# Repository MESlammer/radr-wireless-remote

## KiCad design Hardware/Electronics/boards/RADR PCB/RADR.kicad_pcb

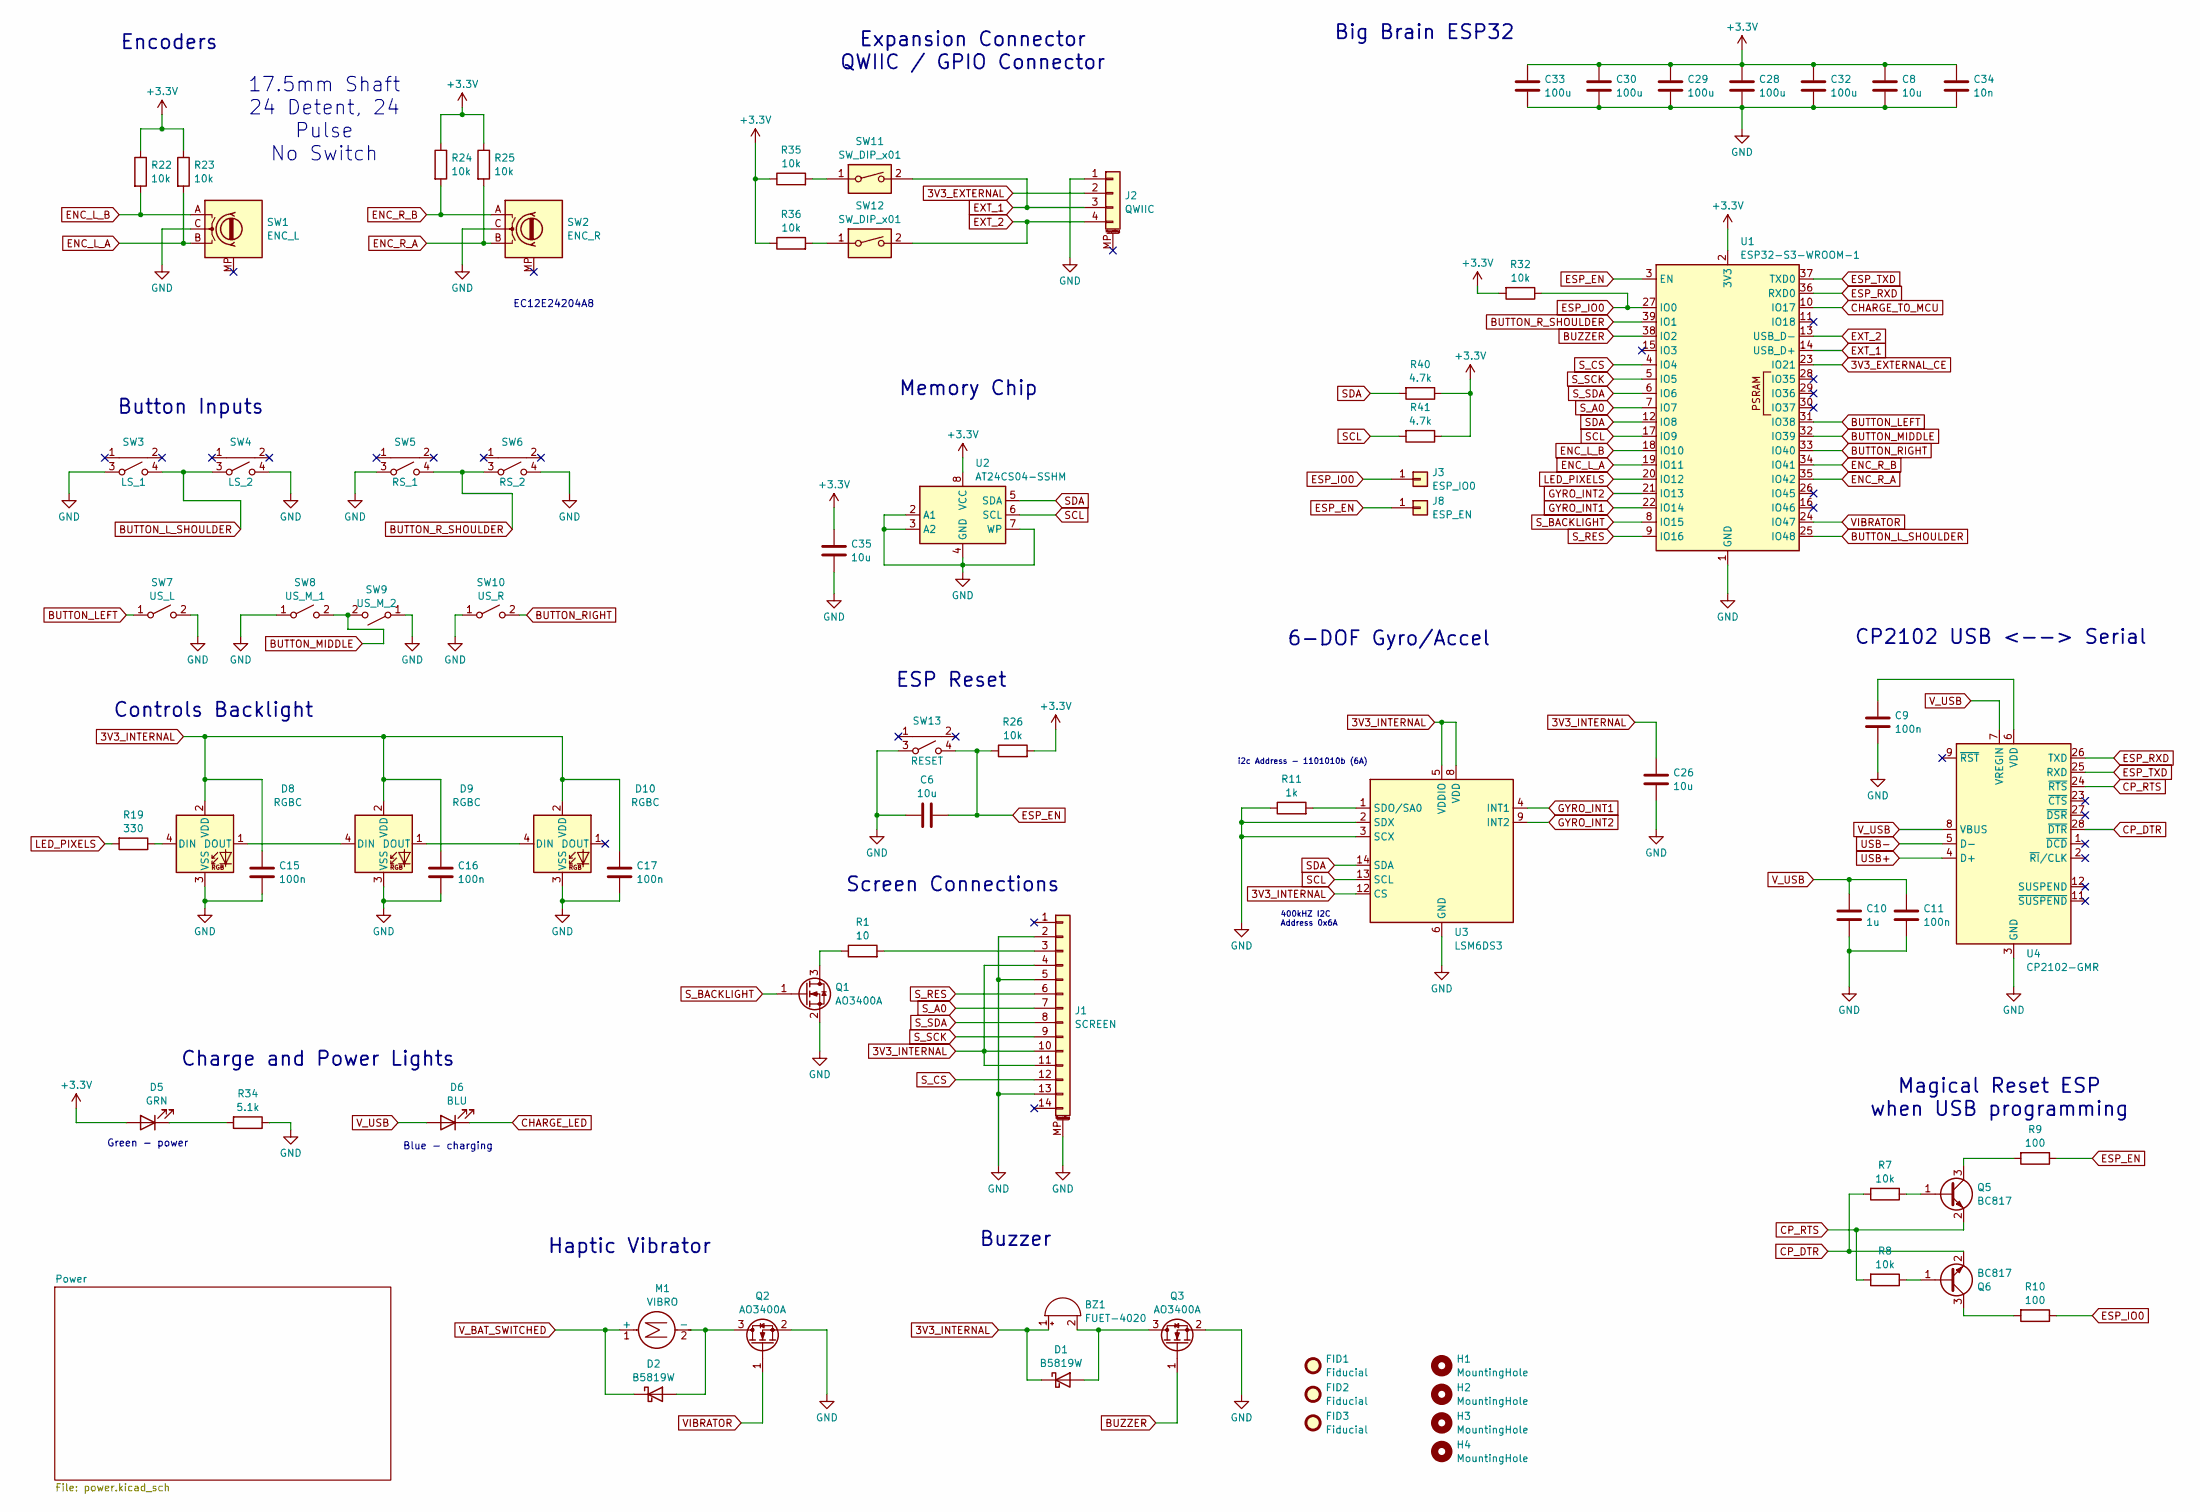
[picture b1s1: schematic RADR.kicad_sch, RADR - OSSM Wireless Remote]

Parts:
BZ1: FUET-4020; Buzzer_FUET-4020_SMD_L4.0-W4.0-P3.50-L; MPN FUET-4020; lcsc-bom-key C391027
C6, C8, C26, C35: 10u; C_0402_1005Metric; MPN CL05A105KA5NQNC; lcsc-bom-key C52923
C9, C11, C15, C16, C17: 100n; C_0402_1005Metric; MPN CL05A104KA5NNNC; lcsc-bom-key C100072
C10: 1u; C_0402_1005Metric; MPN CL05A105KA5NQNC; lcsc-bom-key C52923
C28, C29, C30, C32, C33: 100u; C_1206_3216Metric; MPN CL31A107MQHNNNE; lcsc-bom-key C15008
C34: 10n; C_0402_1005Metric; MPN CL05B103KB5NNNC; lcsc-bom-key C15195
D1, D2: B5819W; D_SOD-123; MPN B5819W; lcsc-bom-key C5345968
D5: GRN; LED_0603_1608Metric; MPN TJ-S1706SW6TGLC2G-A5; lcsc-bom-key C273616
D6: BLU; LED_0603_1608Metric; MPN TJ-S1706SW6TGLC6B-A5; lcsc-bom-key C273617
D8, D9, D10: RGBC; LED_Xinglight_XL-1010RGBC-WS2812B_1.0mm_1.0mm; MPN XL-1010RGBC-2812B; lcsc-bom-key C5349953
FID1, FID2, FID3: Fiducial; Fiducial_1mm_Mask3mm
H1, H2, H3, H4: MountingHole; MountingHole_3.5mm
J1: SCREEN; AFC01-S14FCA-00; MPN AFC01-S14FCA-00; lcsc-bom-key C262663
J2: QWIIC; JST_SH_SM04B-SRSS-TB_1x04-1MP_P1.00mm_Horizontal; MPN SM04B-SRSS-TB(LF)(SN); lcsc-bom-key C160404
J3: ESP_IO0; TestPoint_THTPad_D1.0mm_Drill0.5mm
J8: ESP_EN; TestPoint_THTPad_D1.0mm_Drill0.5mm
M1: VIBRO; Vybronics_VZ30C1T8219732L; MPN Z3OC1T8219731; lcsc-bom-key C2894731
Q1, Q2, Q3: AO3400A; SOT-23; MPN AO3400A; lcsc-bom-key C20917
Q5, Q6: BC817; SOT-23; MPN BC817-25,215; lcsc-bom-key C39828
R1: 10; R_0603_1608Metric; MPN RC0603JR-0710RL; lcsc-bom-key C109317
R7, R8, R22, R23, R24, R25, R26, R32, R35, R36: 10k; R_0402_1005Metric; MPN RC0402FR-0710KL; lcsc-bom-key C60490
R9, R10: 100; R_0402_1005Metric; MPN RC0402FR-07100RL; lcsc-bom-key C106232
R11: 1k; R_0402_1005Metric; MPN RC0402FR-071KL; lcsc-bom-key C106235
R19: 330; R_0402_1005Metric; MPN RC0402FR-07330RL; lcsc-bom-key C105875
R34: 5.1k; R_0402_1005Metric; MPN RC0402FR-075K1L; lcsc-bom-key C105872
R40, R41: 4.7k; R_0402_1005Metric; MPN RC0402FR-074K7L; lcsc-bom-key C105871
SW1: ENC_L; RotaryEncoder_Alps_EC12E_Vertical_H20mm; MPN EC12E24204A8; lcsc-bom-key C470598
SW2: ENC_R; RotaryEncoder_Alps_EC12E_Vertical_H20mm; MPN EC12E24204A8; lcsc-bom-key C470598
SW3: LS_1; SW-SMD_TS24CA; MPN TS24CA; lcsc-bom-key C393942
SW4: LS_2; SW-SMD_TS24CA; MPN TS24CA; lcsc-bom-key C393942
SW5: RS_1; SW-SMD_TS24CA; MPN TS24CA; lcsc-bom-key C393942
SW6: RS_2; SW-SMD_TS24CA; MPN TS24CA; lcsc-bom-key C393942
SW7: US_L; SW_PUSH_6mm; MPN TC-6610-9-260G; lcsc-bom-key C2845257
SW8: US_M_1; SW_PUSH_6mm; MPN TC-6610-9-260G; lcsc-bom-key C2845257
SW9: US_M_2; SW_PUSH_6mm; MPN TC-6610-9-260G; lcsc-bom-key C2845257
SW10: US_R; SW_PUSH_6mm; MPN TC-6610-9-260G; lcsc-bom-key C2845257
SW11, SW12: SW_DIP_x01; SW_DIP_SPSTx01_Slide_2.54-1P_TPGT; MPN 2.54-1P TPGT; lcsc-bom-key C7421519
SW13: RESET; SW-SMD_TS24CA; MPN TS24CA; lcsc-bom-key C393942
U1: ESP32-S3-WROOM-1; MPN C2913202 ESP32-S3-WROOM-1-N16R8 ESPRESS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; lcsc-bom-key C2913202
U2: AT24CS04-SSHM; SOIC-8_3.9x4.9mm_P1.27mm; MPN AT24C04C-SSHM-T; lcsc-bom-key C6205
U3: LSM6DS3; LGA-14_3x2.5mm_P0.5mm_LayoutBorder3x4y; MPN LSM6DS3TR; lcsc-bom-key C95230
U4: CP2102-GMR; QFN-28-1EP_5x5mm_P0.5mm_EP3.35x3.35mm; MPN CP2102-GMR; lcsc-bom-key C6568

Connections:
3V3_EXTERNAL: J2.2; also elsewhere on the board
3V3_EXTERNAL_CE: U1.23 (IO21); also elsewhere on the board
3V3_INTERNAL: BZ1.1 (+), C15.2, C16.2, C17.2, C26.1, D1.1 (K), D8.2 (VDD), D9.2 (VDD), D10.2 (VDD), J1.4, J1.10, J1.11, U3.5 (VDDIO), U3.8 (VDD), U3.12 (CS); also elsewhere on the board
+3.3V: C8.1, C28.1, C29.1, C30.1, C32.1, C33.1, C34.1, C35.1, D5.2 (A), R22.1, R23.1, R24.1, R25.1, R26.2, R32.2, R35.1, R36.1, R40.1, R41.1, U1.2 (3V3), U2.8 (VCC); also elsewhere on the board
BUTTON_LEFT: SW7.1 (A), U1.31 (IO38)
BUTTON_L_SHOULDER: SW3.4 (B), SW4.3 (A), U1.25 (IO48)
BUTTON_MIDDLE: SW8.2 (B), SW9.2 (B), U1.32 (IO39)
BUTTON_RIGHT: SW10.2 (B), U1.33 (IO40)
BUTTON_R_SHOULDER: SW5.4 (B), SW6.3 (A), U1.39 (IO1)
BUZZER: Q3.1 (G), U1.38 (IO2)
CHARGE_LED: D6.1 (K); also elsewhere on the board
CHARGE_TO_MCU: U1.10 (IO17); also elsewhere on the board
CP_DTR: Q6.2 (E), R7.2, U4.28 (~DTR)
CP_RTS: Q5.2 (E), R8.2, U4.24 (~RTS)
ENC_L_A: R23.2, SW1.B, U1.19 (IO11)
ENC_L_B: R22.2, SW1.A, U1.18 (IO10)
ENC_R_A: R25.2, SW2.B, U1.35 (IO42)
ENC_R_B: R24.2, SW2.A, U1.34 (IO41)
ESP_EN: C6.1, J8.1 (Pin_1_1), R9.1, R26.1, SW13.4 (B), U1.3 (EN)
ESP_IO0: J3.1 (Pin_1_1), R10.1, R32.1, U1.27 (IO0)
ESP_RXD: U1.36 (RXD0), U4.26 (TXD)
ESP_TXD: U1.37 (TXD0), U4.25 (RXD)
EXT_1: J2.3, SW11.2, U1.14 (USB_D+)
EXT_2: J2.4, SW12.2, U1.13 (USB_D-)
GND: C6.2, C8.2, C9.2, C10.2, C11.2, C15.1, C16.1, C17.1, C26.2, C28.2, C29.2, C30.2, C32.2, C33.2, C34.2, C35.2, D8.3 (VSS), D9.3 (VSS), D10.3 (VSS), J1.2, J1.5, J1.13, J1.MP (MountPin), J2.1, Q1.2 (S), Q2.2 (S), Q3.2 (S), R11.1, R34.1, SW1.C, SW2.C, SW3.3 (A), SW4.4 (B), SW5.3 (A), SW6.4 (B), SW7.2 (B), SW8.1 (A), SW9.1 (A), SW10.1 (A), SW13.3 (A), U1.1 (GND), U1.40 (GND), U1.41 (GND), U2.2 (A1), U2.3 (A2), U2.4 (GND), U2.7 (WP), U3.2 (SDX), U3.3 (SCX), U3.6 (GND), U3.7 (GND), U4.3 (GND), U4.29 (GND); also elsewhere on the board
GYRO_INT1: U1.22 (IO14), U3.4 (INT1)
GYRO_INT2: U1.21 (IO13), U3.9 (INT2)
LED_PIXELS: R19.2, U1.20 (IO12)
unnamed: BZ1.2 (-), D1.2 (A), Q3.3 (D)
unnamed: D2.2 (A), M1.2 (-), Q2.3 (D)
unnamed: D5.1 (K), R34.2
unnamed: D8.4 (DIN), R19.1
unnamed: D8.1 (DOUT), D9.4 (DIN)
unnamed: D9.1 (DOUT), D10.4 (DIN)
unnamed: J1.3, R1.2
unnamed: Q1.3 (D), R1.1
unnamed: Q5.1 (B), R7.1
unnamed: Q5.3 (C), R9.2
unnamed: Q6.1 (B), R8.1
unnamed: Q6.3 (C), R10.2
unnamed: R35.2, SW11.1
unnamed: R36.2, SW12.1
unnamed: R11.2, U3.1 (SDO/SA0)
unnamed: C9.1, U4.6 (VDD)
SCL: R41.2, U1.17 (IO9), U2.6 (SCL), U3.13 (SCL); also elsewhere on the board
SDA: R40.2, U1.12 (IO8), U2.5 (SDA), U3.14 (SDA); also elsewhere on the board
S_A0: J1.7, U1.7 (IO7)
S_BACKLIGHT: Q1.1 (G), U1.8 (IO15)
S_CS: J1.12, U1.4 (IO4)
S_RES: J1.6, U1.9 (IO16)
S_SCK: J1.9, U1.5 (IO5)
S_SDA: J1.8, U1.6 (IO6)
USB+: U4.4 (D+); also elsewhere on the board
USB-: U4.5 (D-); also elsewhere on the board
VIBRATOR: Q2.1 (G), U1.24 (IO47)
V_BAT_SWITCHED: D2.1 (K), M1.1 (+); also elsewhere on the board
V_USB: C10.1, C11.1, D6.2 (A), U4.7 (VREGIN), U4.8 (VBUS); also elsewhere on the board

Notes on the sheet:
EC12E24204A8
Haptic Vibrator
6-DOF Gyro/Accel
Magical Reset ESP when USB programming
i2c Address - 1101010b (6A)
Button Inputs
Expansion Connector QWIIC / GPIO Connector
Controls Backlight
Big Brain ESP32
Green - power
Memory Chip
ESP Reset
Buzzer
CP2102 USB <--> Serial
400kHZ I2C Address 0x6A
Blue - charging
Screen Connections
Charge and Power Lights
Encoders
17.5mm Shaft 24 Detent, 24 Pulse No Switch

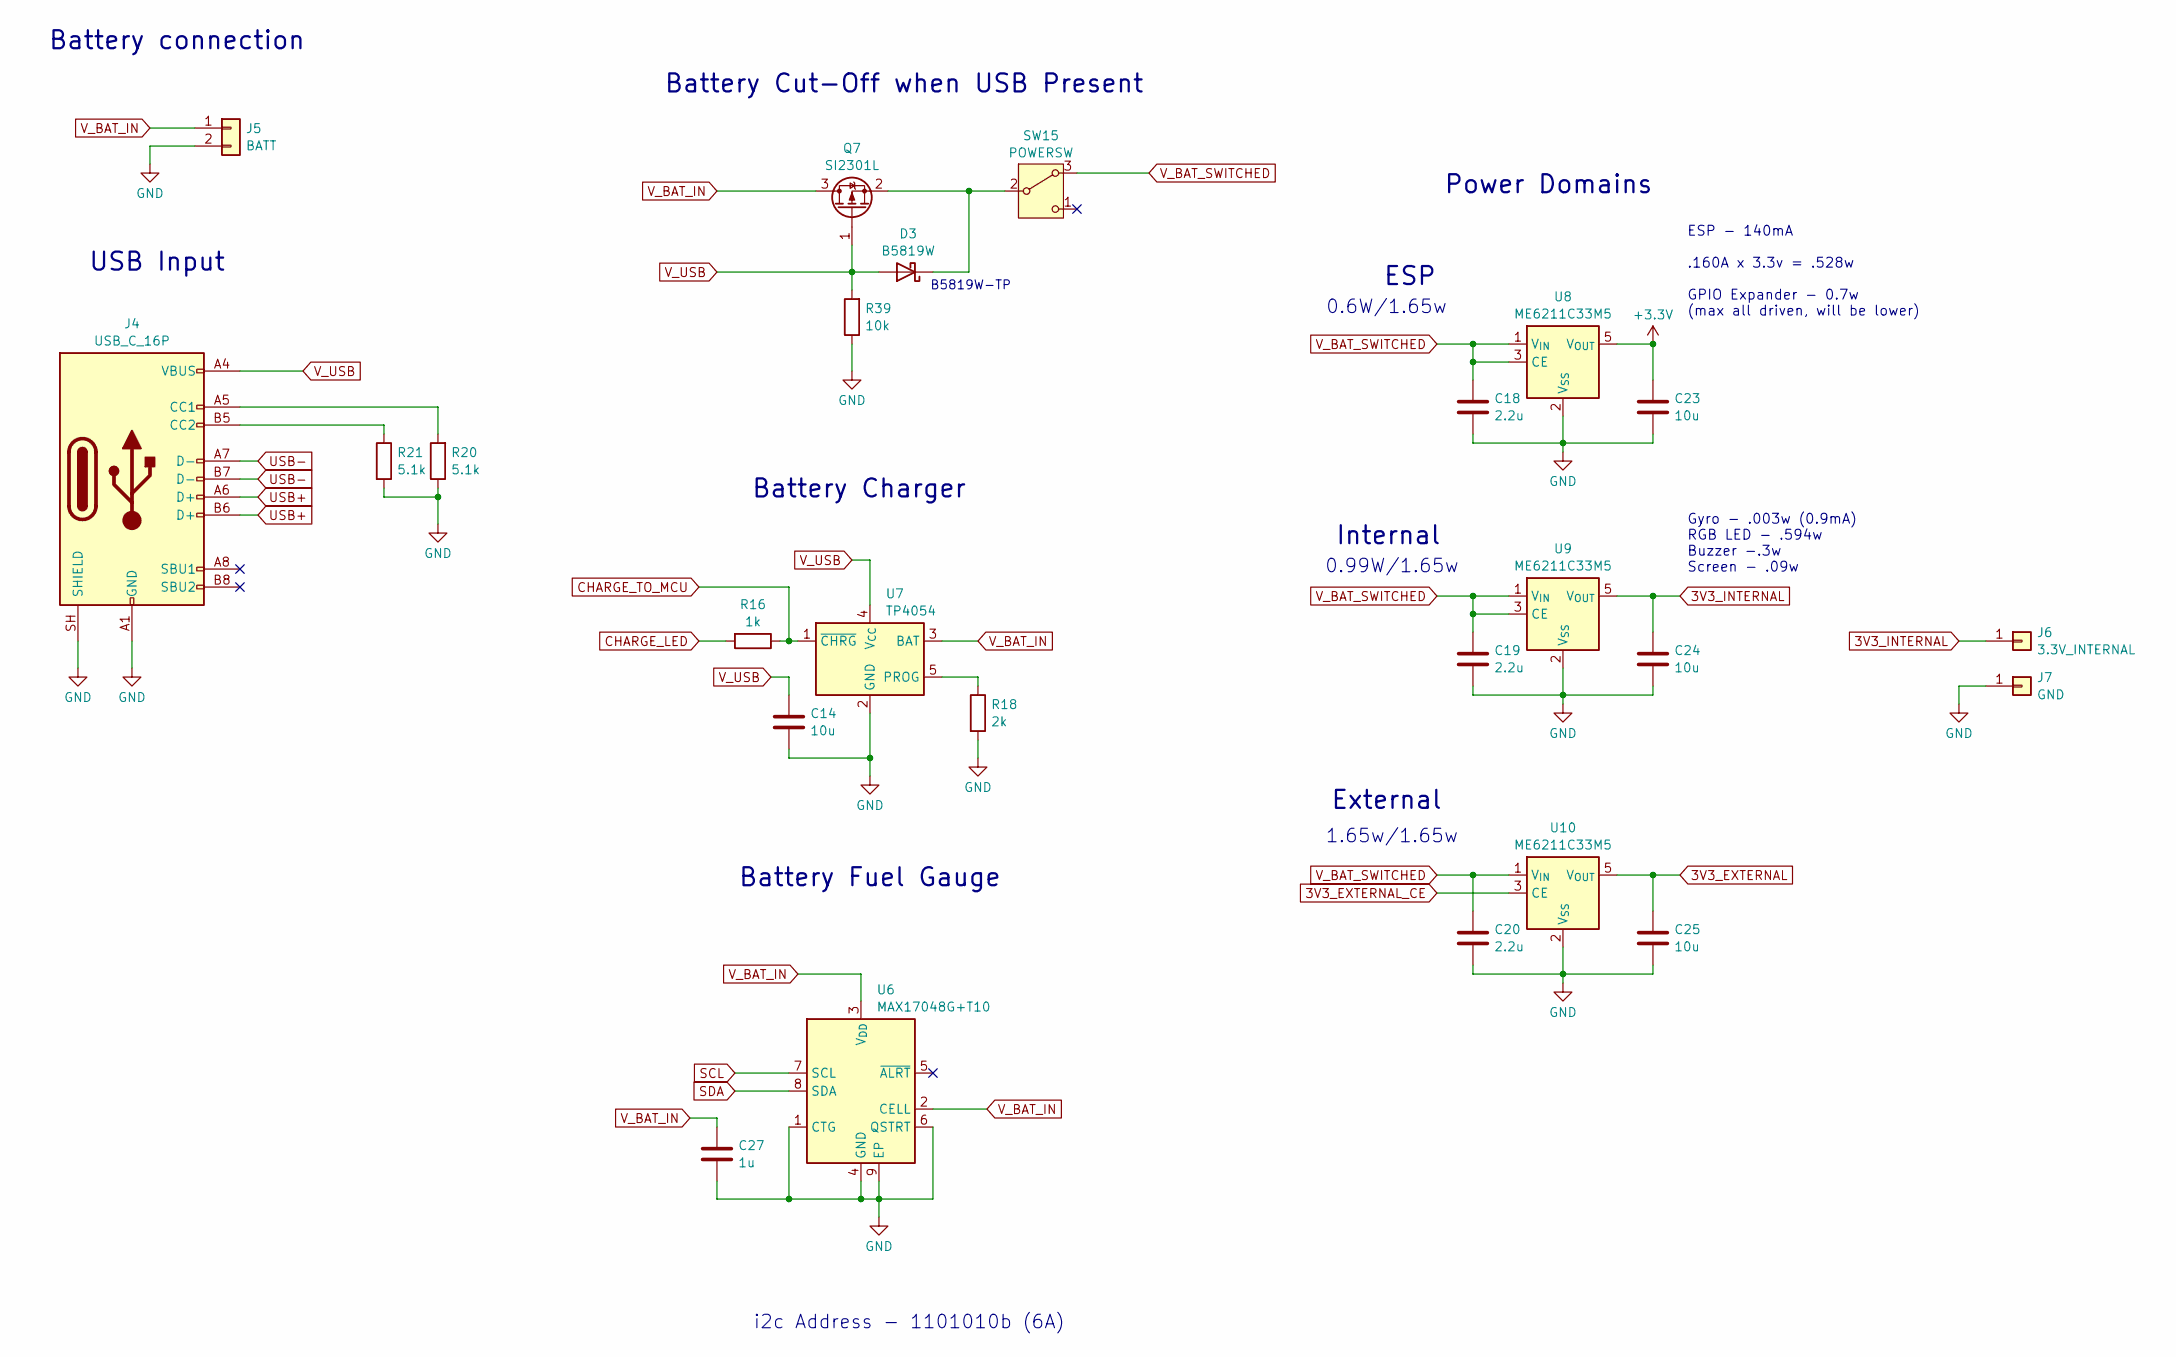
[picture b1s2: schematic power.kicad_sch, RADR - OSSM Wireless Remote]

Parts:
C14, C23, C24, C25: 10u; C_0402_1005Metric; MPN CL05A105KA5NQNC; lcsc-bom-key C52923
C18, C19, C20: 2.2u; C_0402_1005Metric; MPN CL05A225KO5NQNC; lcsc-bom-key C170151
C27: 1u; C_0402_1005Metric; MPN CL05A105KA5NQNC; lcsc-bom-key C52923
D3: B5819W; D_SOD-123; MPN B5819W; lcsc-bom-key C5345968
J4: USB_C_16P; USB_C_Receptacle_HRO_TYPE-C-31-M-12; MPN TYPE-C-31-M-12; lcsc-bom-key C165948
J5: BATT; JST_PH_S2B-PH-K_1x02_P2.00mm_Horizontal; MPN S2B-PH-K(LF)(SN); lcsc-bom-key C265016
J6: 3.3V_INTERNAL; TestPoint_THTPad_2.0x2.0mm_Drill1.0mm
J7: GND; TestPoint_THTPad_2.0x2.0mm_Drill1.0mm
Q7: SI2301L; SOT-23; MPN SI2301; lcsc-bom-key C727151
R16: 1k; R_0402_1005Metric; MPN RC0402FR-071KL; lcsc-bom-key C106235
R18: 2k; R_0402_1005Metric; MPN RC0402FR-072KL; lcsc-bom-key C60488
R20, R21: 5.1k; R_0402_1005Metric; MPN RC0402FR-075K1L; lcsc-bom-key C105872
R39: 10k; R_0402_1005Metric; MPN RC0402FR-0710KL; lcsc-bom-key C60490
SW15: POWERSW; SW_Slide_SPDT_Angled_CK_OS102011MA1Q; MPN SK12D07VG5; lcsc-bom-key C431548
U6: MAX17048G+T10; DFN-8-1EP_2x2mm_P0.5mm_EP0.9x1.5mm; MPN MAX17048G+T10; lcsc-bom-key C2682616
U7: TP4054; SOT-23-5; MPN TP4054; lcsc-bom-key C5381776
U8, U9, U10: ME6211C33M5; SOT-23-5; MPN ME6211C33R5G; lcsc-bom-key C235316

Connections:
3V3_EXTERNAL: C25.1, U10.5 (V_{OUT}); also elsewhere on the board
3V3_EXTERNAL_CE: U10.3 (CE); also elsewhere on the board
3V3_INTERNAL: C24.1, J6.1 (Pin_1_1), U9.5 (V_{OUT}); also elsewhere on the board
+3.3V: C23.1, U8.5 (V_{OUT}); also elsewhere on the board
CHARGE_LED: R16.2; also elsewhere on the board
CHARGE_TO_MCU: R16.1, U7.1 (~CHRG); also elsewhere on the board
GND: C14.2, C18.2, C19.2, C20.2, C23.2, C24.2, C25.2, C27.2, J4.A1 (GND), J4.A12 (GND), J4.B1 (GND), J4.B12 (GND), J4.SH (SHIELD), J5.2, J7.1 (Pin_1_1), R18.2, R20.1, R21.2, R39.1, U6.1 (CTG), U6.4 (GND), U6.6 (QSTRT), U6.9 (EP), U7.2 (GND), U8.2 (V_{SS}), U9.2 (V_{SS}), U10.2 (V_{SS}); also elsewhere on the board
unnamed: D3.1 (K), Q7.2 (S), SW15.2 (B)
unnamed: J4.A5 (CC1), R20.2
unnamed: J4.B5 (CC2), R21.1
unnamed: R18.1, U7.5 (PROG)
SCL: U6.7 (SCL); also elsewhere on the board
SDA: U6.8 (SDA); also elsewhere on the board
USB+: J4.A6 (D+), J4.B6 (D+); also elsewhere on the board
USB-: J4.A7 (D-), J4.B7 (D-); also elsewhere on the board
V_BAT_IN: C27.1, J5.1, Q7.3 (D), U6.2 (CELL), U6.3 (V_{DD}), U7.3 (BAT)
V_BAT_SWITCHED: C18.1, C19.1, C20.1, SW15.3 (A), U8.1 (V_{IN}), U8.3 (CE), U9.1 (V_{IN}), U9.3 (CE), U10.1 (V_{IN}); also elsewhere on the board
V_USB: C14.1, D3.2 (A), J4.A4 (VBUS), J4.A9 (VBUS), J4.B4 (VBUS), J4.B9 (VBUS), Q7.1 (G), R39.2, U7.4 (V_{CC}); also elsewhere on the board

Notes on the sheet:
1.65w/1.65w
Battery connection
Battery Charger
0.99W/1.65w
Power Domains
Battery Fuel Gauge
External
B5819W-TP
ESP
USB Input
Battery Cut-Off when USB Present
i2c Address - 1101010b (6A)
Internal
0.6W/1.65w
ESP - 140mA .160A x 3.3v = .528w GPIO Expander - 0.7w (max all driven, will be lower)
Gyro - .003w (0.9mA) RGB LED - .594w Buzzer -.3w Screen - .09w

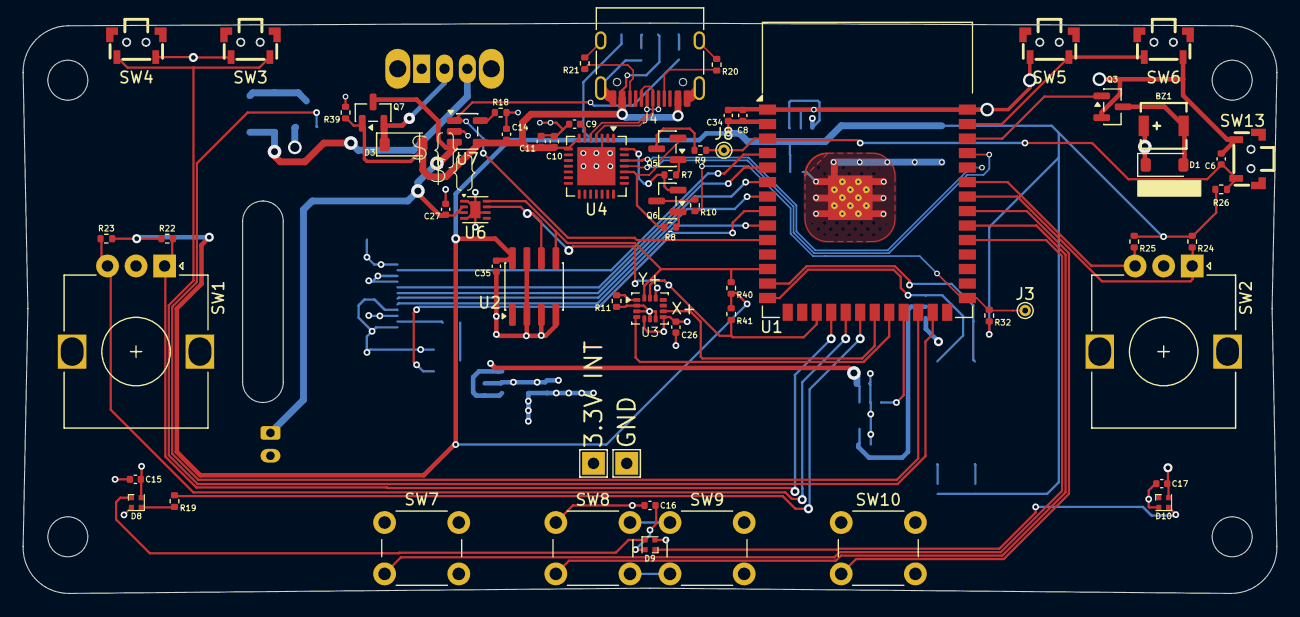
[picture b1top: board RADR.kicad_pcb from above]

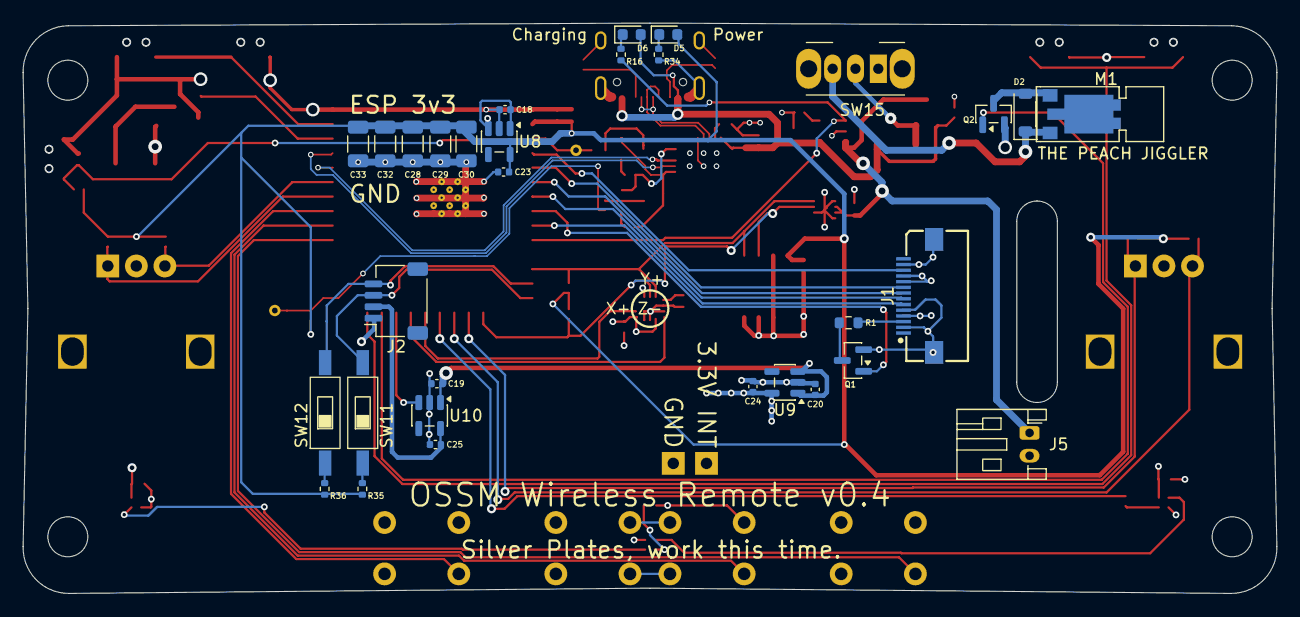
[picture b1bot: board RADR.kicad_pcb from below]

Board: 4 copper layers, 109.8 x 50.0 mm, 98 parts (31 on the bottom side), 62 nets.

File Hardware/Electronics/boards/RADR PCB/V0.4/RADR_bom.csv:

"Reference","Qty","Value","Footprint","Datasheet","lcsc-bom-key","MPN","MFG","Characteristics","DNP","Exclude from BOM","Exclude from Board"
"BZ1","1","FUET-4020","RADR:Buzzer_FUET-4020_SMD_L4.0-W4.0-P3.50-L","https://www.lcsc.com/datasheet/C391027.pdf","C391027","FUET-4020","FUET","","","",""
"C6,C8,C14,C23,C24,C25,C26,C35","8","10u","Capacitor_SMD:C_0402_1005Metric","https://www.lcsc.com/datasheet/C52923.pdf","C52923","CL05A105KA5NQNC","Samsung Electro-Mechanics","","","",""
"C9,C11,C15,C16,C17","5","100n","Capacitor_SMD:C_0402_1005Metric","https://www.lcsc.com/datasheet/C100072.pdf","C100072","CL05A104KA5NNNC","Samsung Electro-Mechanics","","","",""
"C10,C27","2","1u","Capacitor_SMD:C_0402_1005Metric","https://www.lcsc.com/datasheet/C52923.pdf","C52923","CL05A105KA5NQNC","Samsung Electro-Mechanics","","","",""
"C18,C19,C20","3","2.2u","Capacitor_SMD:C_0402_1005Metric","https://www.lcsc.com/datasheet/C170151.pdf","C170151","CL05A225KO5NQNC","Samsung Electro-Mechanics","","","",""
"C28,C29,C30,C32,C33","5","100u","Capacitor_SMD:C_1206_3216Metric","https://www.lcsc.com/datasheet/C15008.pdf","C15008","CL31A107MQHNNNE","Samsung Electro-Mechanics","","","",""
"C34","1","10n","Capacitor_SMD:C_0402_1005Metric","https://www.lcsc.com/datasheet/C15195.pdf","C15195","CL05B103KB5NNNC","CL05B103KB5NNNC","","","",""
"D1,D2,D3","3","B5819W","Diode_SMD:D_SOD-123","https://www.lcsc.com/datasheet/C5345968.pdf","C5345968","B5819W","HXY MOSFET","","","",""
"D5","1","GRN","LED_SMD:LED_0603_1608Metric","https://www.lcsc.com/datasheet/C273616.pdf","C273616","TJ-S1706SW6TGLC2G-A5","TOGIALED","Green","","",""
"D6","1","BLU","LED_SMD:LED_0603_1608Metric","https://www.lcsc.com/datasheet/C273617.pdf","C273617","TJ-S1706SW6TGLC6B-A5","TOGIALED","Blue","","",""
"D8,D9,D10","3","RGBC","LED_SMD:LED_XL-1010RGBC-WS2812B_1.0x1.0mm","https://www.lcsc.com/datasheet/C5349953.pdf","C5349953","XL-1010RGBC-2812B","XINGLIGHT","","","",""
"J1","1","SCREEN","RADR:AFC01-S14FCA-00","https://www.lcsc.com/datasheet/C262663.pdf","C262663","AFC01-S14FCA-00","JUSHUO","","","",""
"J2","1","QWIIC","Connector_JST:JST_SH_SM04B-SRSS-TB_1x04-1MP_P1.00mm_Horizontal","https://www.lcsc.com/datasheet/C160404.pdf","C160404","SM04B-SRSS-TB(LF)(SN)","JST","","","",""
"J4","1","USB_C_16P","Connector_USB:USB_C_Receptacle_HRO_TYPE-C-31-M-12","https://www.usb.org/sites/default/files/documents/usb_type-c.zip","C165948","TYPE-C-31-M-12","Korean Hroparts Elec","","","",""
"J5","1","BATT","Connector_JST:JST_PH_S2B-PH-K_1x02_P2.00mm_Horizontal","https://www.lcsc.com/datasheet/C265016.pdf","C265016","S2B-PH-K(LF)(SN)","JST","","","",""
"M1","1","VIBRO","Motors:Vybronics_VZ30C1T8219732L","https://www.lcsc.com/datasheet/C2894731.pdf","C2894731","Z3OC1T8219731","KOTL","","","",""
"Q1,Q2,Q3","3","AO3400A","Package_TO_SOT_SMD:SOT-23","http://www.aosmd.com/pdfs/datasheet/AO3400A.pdf","C20917","AO3400A","AOS","","","",""
"Q5,Q6","2","BC817","Package_TO_SOT_SMD:SOT-23","https://www.lcsc.com/datasheet/C52801.pdf","C39828","BC817-25,215","Nexperia","","","",""
"Q7","1","SI2301L","Package_TO_SOT_SMD:SOT-23","https://atta.szlcsc.com/upload/public/pdf/source/20200827/C7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","C727151","SI2301","TWGMC","","","",""
"R1","1","10","Resistor_SMD:R_0603_1608Metric","https://www.lcsc.com/datasheet/C109317.pdf","C109317","RC0603JR-0710RL","YAGEO","","","",""
"R7,R8,R22,R23,R24,R25,R26,R32,R35,R36,R39","11","10k","Resistor_SMD:R_0402_1005Metric","https://www.lcsc.com/datasheet/C60490.pdf","C60490","RC0402FR-0710KL","YAGEO","","","",""
"R9,R10","2","100","Resistor_SMD:R_0402_1005Metric","https://www.lcsc.com/datasheet/C106232.pdf","C106232","RC0402FR-07100RL","YAGEO","","","",""
"R11,R16","2","1k","Resistor_SMD:R_0402_1005Metric","https://www.lcsc.com/datasheet/C106235.pdf","C106235","RC0402FR-071KL","YAGEO","","","",""
"R18","1","2k","Resistor_SMD:R_0402_1005Metric","https://www.lcsc.com/datasheet/C60488.pdf","C60488","RC0402FR-072KL","YAGEO","","","",""
"R19","1","330","Resistor_SMD:R_0402_1005Metric","https://www.lcsc.com/datasheet/C105875.pdf","C105875","RC0402FR-07330RL","YAGEO","","","",""
"R20,R21,R34","3","5.1k","Resistor_SMD:R_0402_1005Metric","https://www.lcsc.com/datasheet/C105872.pdf","C105872","RC0402FR-075K1L","YAGEO","","","",""
"R40,R41","2","4.7k","Resistor_SMD:R_0402_1005Metric","https://www.lcsc.com/datasheet/C105871.pdf","C105871","RC0402FR-074K7L","YAGEO","","","",""
"SW1","1","ENC_L","Rotary_Encoder:RotaryEncoder_Alps_EC12E_Vertical_H20mm","https://www.lcsc.com/datasheet/C470598.pdf","C470598","EC12E24204A8","ALPSALPINE","","","",""
"SW2","1","ENC_R","Rotary_Encoder:RotaryEncoder_Alps_EC12E_Vertical_H20mm","https://www.lcsc.com/datasheet/C470598.pdf","C470598","EC12E24204A8","ALPSALPINE","","","",""
"SW3","1","LS_1","SW_Push_TS24CA","https://www.lcsc.com/datasheet/C393942.pdf","C393942","TS24CA","SHOU HAN","","","",""
"SW4","1","LS_2","SW_Push_TS24CA","https://www.lcsc.com/datasheet/C393942.pdf","C393942","TS24CA","SHOU HAN","","","",""
"SW5","1","RS_1","SW_Push_TS24CA","https://www.lcsc.com/datasheet/C393942.pdf","C393942","TS24CA","SHOU HAN","","","",""
"SW6","1","RS_2","SW_Push_TS24CA","https://www.lcsc.com/datasheet/C393942.pdf","C393942","TS24CA","SHOU HAN","","","",""
"SW7","1","US_L","Button_Switch_THT:SW_PUSH_6mm","https://www.lcsc.com/datasheet/C2845257.pdf","C2845257","TC-6610-9-260G","HCTL","","","",""
"SW8","1","US_M_1","Button_Switch_THT:SW_PUSH_6mm","https://www.lcsc.com/datasheet/C2845257.pdf","C2845257","TC-6610-9-260G","HCTL","","","",""
"SW9","1","US_M_2","Button_Switch_THT:SW_PUSH_6mm","https://www.lcsc.com/datasheet/C2845257.pdf","C2845257","TC-6610-9-260G","HCTL","","","",""
"SW10","1","US_R","Button_Switch_THT:SW_PUSH_6mm","https://www.lcsc.com/datasheet/C2845257.pdf","C2845257","TC-6610-9-260G","HCTL","","","",""
"SW11,SW12","2","SW_DIP_x01","RADR:SW_DIP_SPSTx01_Slide_2.54-1P_TPGT","https://www.lcsc.com/datasheet/C7421519.pdf","C7421519","2.54-1P TPGT","SHOU HAN","","","",""
"SW13","1","RESET","SW_Push_TS24CA","https://www.lcsc.com/datasheet/C393942.pdf","C393942","TS24CA","SHOU HAN","","","",""
"SW15","1","POWERSW","Button_Switch_THT:SW_Slide_SPDT_Angled_CK_OS102011MA1Q","https://www.lcsc.com/datasheet/C431548.pdf","C431548","SK12D07VG5","SHOU HAN","","","",""
"U1","1","ESP32-S3-WROOM-1","RF_Module:ESP32-S3-WROOM-1","https://www.espressif.com/sites/default/files/documentation/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","C2913202","C2913202 ESP32-S3-WROOM-1-N16R8 ESPRESSIF N16R8","ESPRESSIF","N16R8","","",""
"U2","1","AT24CS04-SSHM","Package_SO:SOIC-8_3.9x4.9mm_P1.27mm","http://ww1.microchip.com/downloads/en/DeviceDoc/Atmel-8766-S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","C6205","AT24C04C-SSHM-T","MICROCHIP","","","",""
"U3","1","LSM6DS3","Package_LGA:LGA-14_3x2.5mm_P0.5mm_LayoutBorder3x4y","https://www.st.com/resource/en/datasheet/lsm6ds3tr-c.pdf","C95230","LSM6DS3TR","ST","","","",""
"U4","1","CP2102-GMR","Package_DFN_QFN:QFN-28-1EP_5x5mm_P0.5mm_EP3.35x3.35mm","https://www.silabs.com/documents/public/data-sheets/CP2102-9.pdf","C6568","CP2102-GMR","SILICON LABS","","","",""
"U6","1","MAX17048G+T10","Package_DFN_QFN:DFN-8-1EP_2x2mm_P0.5mm_EP0.9x1.5mm","https://atta.szlcsc.com/upload/public/pdf/source/20210106/C2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","C2682616","MAX17048G+T10","MAXIM","","","",""
"U7","1","TP4054","Package_TO_SOT_SMD:SOT-23-5","http://toppwr.com/uploadfile/file/20230304/640302a47b738.pdf","C5381776","TP4054","JSMSEMI","","","",""
"U8,U9,U10","3","ME6211C33M5","Package_TO_SOT_SMD:SOT-23-5","https://www.lcsc.com/datasheet/lcsc_datasheet_2304140030_MIC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","C235316","ME6211C33R5G","MICRONE","","","",""

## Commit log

2026-02-05 use littlefs.bin instead
2026-02-05 docs
2026-02-05 Device Search and Update
2026-02-05 mermaid graphs
2026-02-05 temp
2026-02-05 AUTO: Release new Alpha version 1.0.24 (#77)
2026-02-05 AUTO: Version bump 1.0.26
2026-02-05 AUTO: Version bump 1.0.27
2026-02-10 docs: sync radr documentation from docs repo
2026-02-10 AUTO: Version bump 1.0.29
2026-02-16 RADR firmware manifest.json
2026-02-16 AUTO: Version bump 1.0.33
2026-03-04 AUTO: Version bump 1.0.35
2026-03-24 AUTO: Version bump 1.0.36
2026-03-26 fix release
2026-03-30 Phase 2 cont.: Fixing crashes and stability issues
2026-03-30 Phase 1: UI bug fixes to the tabs and menu item placement + future TODO
2026-03-30 Phase 2: initial commit
2026-03-30 Phase 3.1: wifi provisioning from the RADR to ossm
2026-03-30 Phase 3: completed all the features including the OSSm pairing to the dashboard.
2026-04-01 AUTO: Version bump 1.0.38
2026-04-06 Apply Update buffer data structure to std::array
2026-04-12 Upload KiCAD sources
    Upload board sources as KiCAD project
2026-04-14 fabrication files for 0.4
2026-04-23 AUTO: Version bump 1.0.39
